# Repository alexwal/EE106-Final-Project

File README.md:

# Zumy Maze Solver
Please check out our [project website]!

[project website]: http://sites.google.com/view/zumymazesolver

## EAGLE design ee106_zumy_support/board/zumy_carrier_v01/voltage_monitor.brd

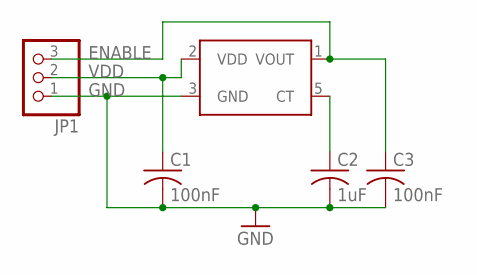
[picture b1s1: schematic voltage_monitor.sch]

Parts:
C1, C3: 100nF; C1206
C2: 1uF; C1206
JP1: PINHD-1X3; 1X03
U$1: BD5260G; SOT23-5

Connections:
ENABLE: C3.1, JP1.3, U$1.1 (VOUT)
GND: C1.2, C2.2, C3.2, JP1.1, U$1.3 (GND)
unnamed: C2.1, U$1.5 (CT)
VDD: C1.1, JP1.2, U$1.2 (VDD)

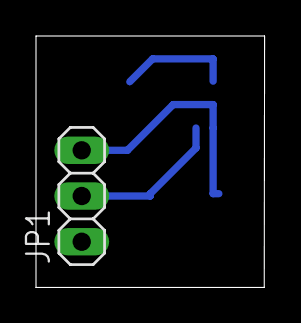
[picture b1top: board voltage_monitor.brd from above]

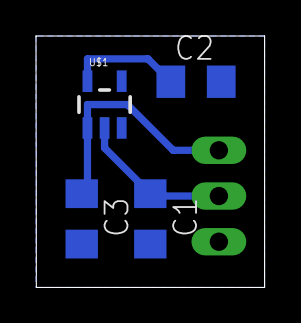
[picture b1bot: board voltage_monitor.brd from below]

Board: 2 copper layers, 12.7 x 14.0 mm, 5 parts (4 on the bottom side), 4 nets.

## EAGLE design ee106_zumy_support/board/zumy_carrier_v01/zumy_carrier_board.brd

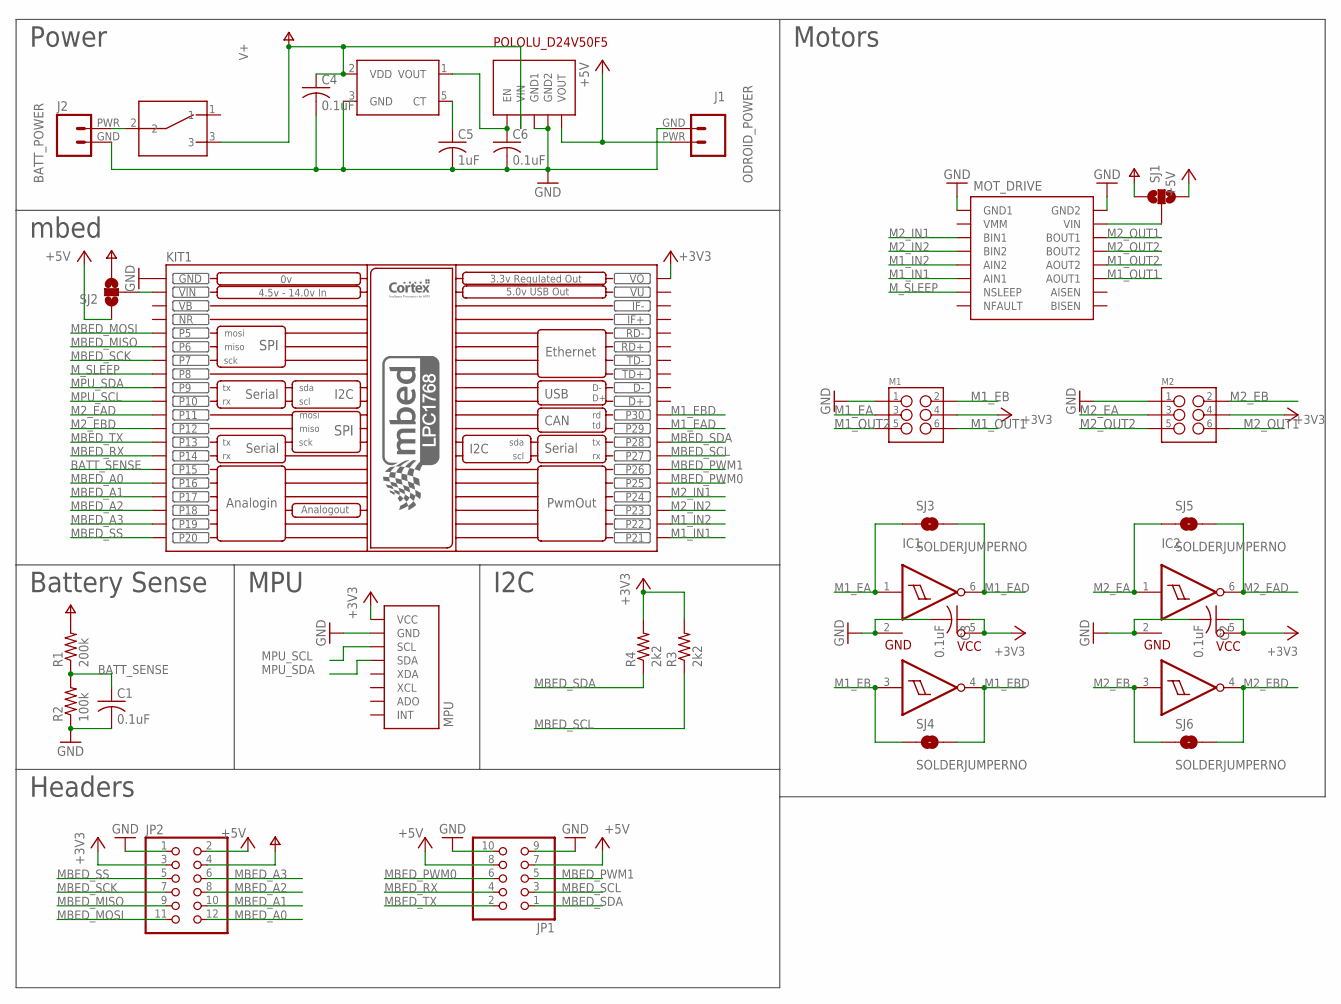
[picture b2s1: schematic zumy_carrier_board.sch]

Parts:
C1, C2, C3, C4, C6: 0.1uF; C1206
C5: 1uF; C1206
IC1, IC2: SN74AUP2G17; SC-70-6
J1: ODROID_POWER; ODOIRD_PWR
J2: BATT_POWER
JP1: PINHD-2X5; 2X05
JP2: PINHD-2X6; 2X06
KIT1: MBED_NXP_LPC1768; MBED-KIT
M1, M2: M03X2SHROUD; 2X3-SHROUDED
MOT_DRIVE: POLOLU_DRV8833_MODULE
MPU: ITG/MPU_MODULE
R1: 200k; R1206
R2: 100k; R1206
R3, R4: 2k2; R1206
SJ1, SJ2: SOLDERJUMPER_2WAYT; SJ_2
SJ3, SJ4, SJ5, SJ6: SOLDERJUMPERNO; SJ_2S-NO
SW1: 500SSP1S1M6QEA; 500SSP1S1M6QEA_SWITCH
U$2: BD5260G; SOT23-5
U$5: POLOLU_D24V50F5

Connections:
+3V3: C2.1, C3.1, IC1.5 (VCC), IC2.5 (VCC), JP2.3, KIT1.VOUT (VO), M1.4, M2.4, MPU.VCC, R3.2, R4.2
+5V: J1.PWR, JP1.7, JP1.8, JP2.2, SJ1.3, SJ2.1, U$5.VOUT
BATT_SENSE: C1.1, KIT1.P$15 (P15), R1.1, R2.2
GND: C1.2, C2.2, C3.2, C4.2, C5.2, C6.2, IC1.2 (GND), IC2.2 (GND), J1.GND, J2.GND, JP1.9, JP1.10, JP2.1, KIT1.GND, M1.1, M2.1, MOT_DRIVE.GND1, MOT_DRIVE.GND2, MPU.GND, R2.1, U$2.3 (GND), U$5.GND1, U$5.GND2
M1_EA: IC1.1 (1A), M1.3, SJ3.1
M1_EAD: IC1.6 (1Y), KIT1.P$29 (P29), SJ3.2
M1_EB: IC1.3 (2A), M1.2, SJ4.1
M1_EBD: IC1.4 (2Y), KIT1.P$30 (P30), SJ4.2
M1_IN1: KIT1.P$21 (P21), MOT_DRIVE.AIN1
M1_IN2: KIT1.P$22 (P22), MOT_DRIVE.AIN2
M1_OUT1: M1.6, MOT_DRIVE.AOUT1
M1_OUT2: M1.5, MOT_DRIVE.AOUT2
M2_EA: IC2.1 (1A), M2.3, SJ5.1
M2_EAD: IC2.6 (1Y), KIT1.P$11 (P11), SJ5.2
M2_EB: IC2.3 (2A), M2.2, SJ6.1
M2_EBD: IC2.4 (2Y), KIT1.P$12 (P12), SJ6.2
M2_IN1: KIT1.P$24 (P24), MOT_DRIVE.BIN1
M2_IN2: KIT1.P$23 (P23), MOT_DRIVE.BIN2
M2_OUT1: M2.6, MOT_DRIVE.BOUT1
M2_OUT2: M2.5, MOT_DRIVE.BOUT2
MBED_A0: JP2.12, KIT1.P$16 (P16)
MBED_A1: JP2.10, KIT1.P$17 (P17)
MBED_A2: JP2.8, KIT1.P$18 (P18)
MBED_A3: JP2.6, KIT1.P$19 (P19)
MBED_MISO: JP2.9, KIT1.P$6 (P6)
MBED_MOSI: JP2.11, KIT1.P$5 (P5)
MBED_PWM0: JP1.6, KIT1.P$25 (P25)
MBED_PWM1: JP1.5, KIT1.P$26 (P26)
MBED_RX: JP1.4, KIT1.P$14 (P14)
MBED_SCK: JP2.7, KIT1.P$7 (P7)
MBED_SCL: JP1.3, KIT1.P$27 (P27), R3.1
MBED_SDA: JP1.1, KIT1.P$28 (P28), R4.1
MBED_SS: JP2.5, KIT1.P$20 (P20)
MBED_TX: JP1.2, KIT1.P$13 (P13)
MPU_SCL: KIT1.P$10 (P10), MPU.SCL
MPU_SDA: KIT1.P$9 (P9), MPU.SDA
M_SLEEP: KIT1.P$8 (P8), MOT_DRIVE.NSLEEP
unnamed: KIT1.VIN, SJ2.2
unnamed: J2.PWR, SW1.2
unnamed: MOT_DRIVE.VIN, SJ1.2
unnamed: C6.1, U$2.1 (VOUT), U$5.EN
unnamed: C5.1, U$2.5 (CT)
NR: KIT1.NR
V+: C4.1, JP2.4, R1.2, SJ1.1, SJ2.3, SW1.3, U$2.2 (VDD), U$5.VIN
VB: KIT1.VB
VU: KIT1.VU

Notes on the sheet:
Motors
Power
mbed
MPU
I2C
Headers
Battery Sense

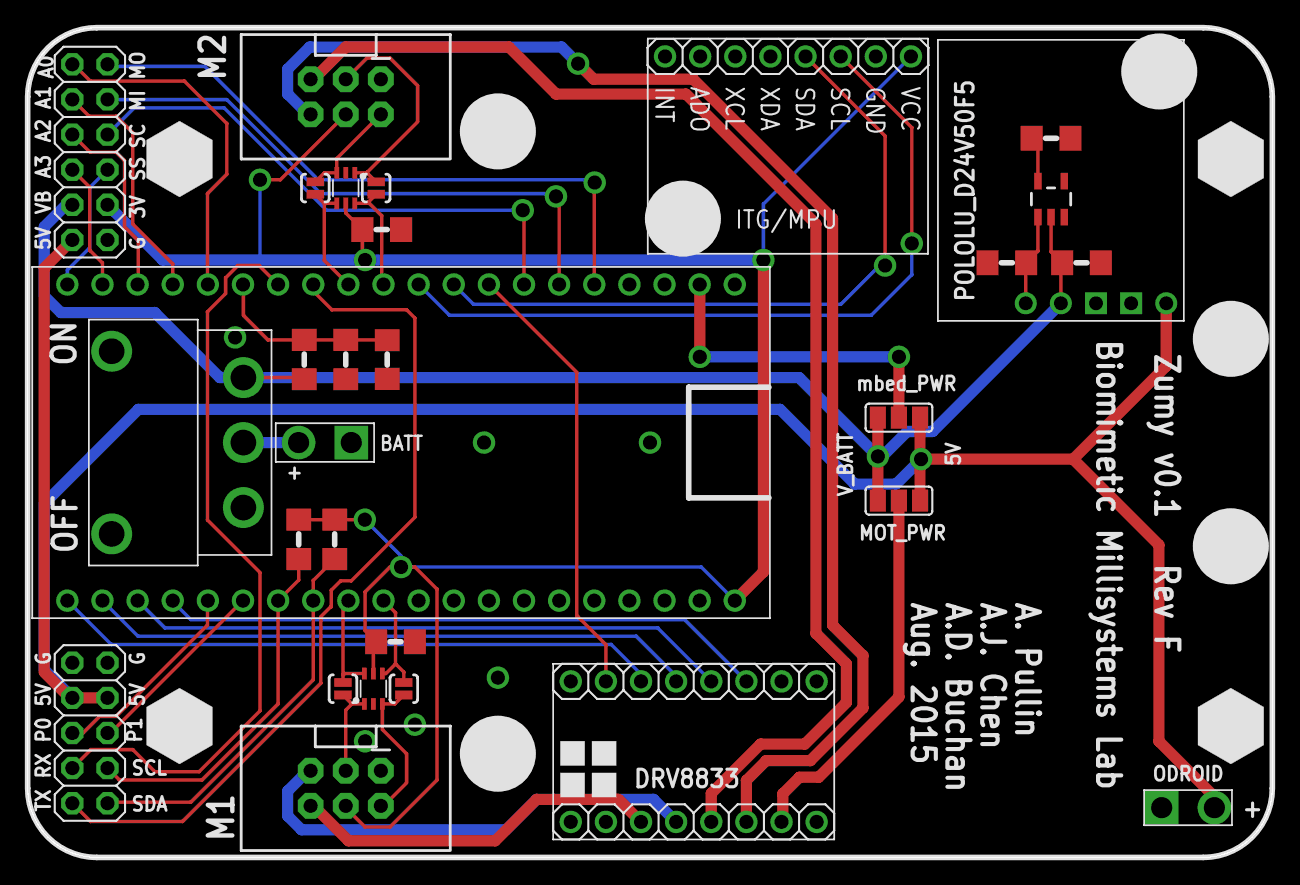
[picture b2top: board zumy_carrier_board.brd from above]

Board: 2 copper layers, 90.0 x 60.0 mm, 32 parts (0 on the bottom side), 43 nets.

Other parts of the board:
U$1: CHASSIS_STANDOFF
U$4: STANDOFF_POSITION

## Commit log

2016-12-05 working IR read
2016-12-05 IR sensor works, zumy rotates
2016-12-05 cleaned up method names, no functional changes
2016-12-06 zumy turns in response to IR sensor readings
2016-12-07 cleaned up code, added comments and NEWs
2016-12-07 fixed spacing
2016-12-09 combining received funcs
2016-12-10 before alex and dan
2016-12-11 switching computers
2016-12-11 adding files
2016-12-11 code that worked on both mazes
2016-12-13 minor bug fix

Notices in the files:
parts and their libraries:
SparkFun-Connectors: Licensing: Creative Commons ShareAlike 4.0 International - https://creativecommons.org/licenses/by-sa/4.0
SparkFun-Passives: Licensing: CC v3.0 Share-Alike You are welcome to use this library for commercial purposes.
biomimetic: UC Regents. All rights reserved.
